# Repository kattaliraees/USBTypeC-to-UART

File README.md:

# USBTypeC-to-UART
USB Type C to Serial port convertor boards for new MacBooks and other laptops

- KiCad Proect
- CP2102N based

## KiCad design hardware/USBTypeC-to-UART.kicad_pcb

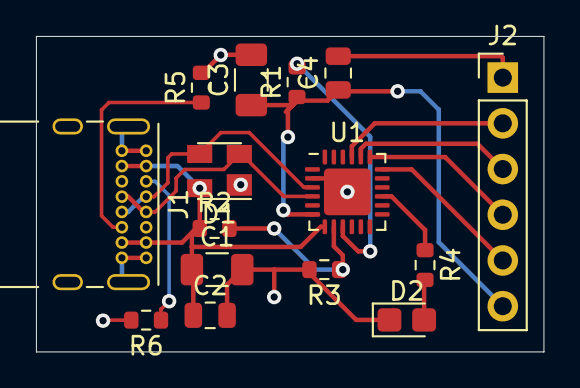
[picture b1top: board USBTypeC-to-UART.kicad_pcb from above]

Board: 2 copper layers, 28.2 x 17.5 mm, 15 parts (0 on the bottom side), 15 nets.

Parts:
C1, C3: 4.7uf; C_1206_3216Metric
C2, C4: 100nf; C_0805_2012Metric
D1: SP0503BAHTG; SOT-143
D2: LED; LED_0805_2012Metric_Castellated
J1: USB_C_Receptacle_USB2.0; USB_C_Receptacle_GCT_USB4085
J2: Conn_01x06_Male; PinHeader_1x06_P2.54mm_Vertical
R1: 1.1K; R_0603_1608Metric
R2: 22K; R_0603_1608Metric
R3: 47K; R_0603_1608Metric
R4: 220; R_0603_1608Metric
R5, R6: 5.1K; R_0603_1608Metric
U1: CP2102N-A01-GQFN24; QFN-24-1EP_4x4mm_P0.5mm_EP2.6x2.6mm

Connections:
/D+: D1.3, J1.A6, J1.B6, U1.3
/D-: D1.2, J1.A7, J1.B7, U1.4
/SUSPENDn: R4.1, U1.15
/VBUS: C1.1, C2.1, D1.4, J1.A4, J1.A9, J1.B4, J1.B9, R2.1, U1.7
GND: C1.2, C2.2, C3.2, C4.2, D1.1, D2.1, J1.A1, J1.A12, J1.B1, J1.B12, J1.S1, J2.1, R3.2, R5.2, R6.2, U1.2, U1.25
unnamed: D2.2, R4.2
unnamed: J1.A5, R6.1
unnamed: J1.B5, R5.1
unnamed: J2.2, U1.21
unnamed: J2.3, U1.20
unnamed: J2.4, U1.19
unnamed: J2.5, U1.18
unnamed: R1.2, U1.9
unnamed: R2.2, R3.1, U1.8
VDD: C3.1, C4.1, J2.6, R1.1, U1.6

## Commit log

2019-10-14 First
2019-10-15 layout
2019-10-15 description
2019-10-16 rendered 3d model
2021-02-10 usb connector 3d model
